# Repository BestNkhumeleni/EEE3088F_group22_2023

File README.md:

# EEE3088F_group22_2023
 With Best Nkhumeleni doing the STM32 intergration.
 Loic kibambo doing the power circutes.
 Maisha magavha doing the sensing

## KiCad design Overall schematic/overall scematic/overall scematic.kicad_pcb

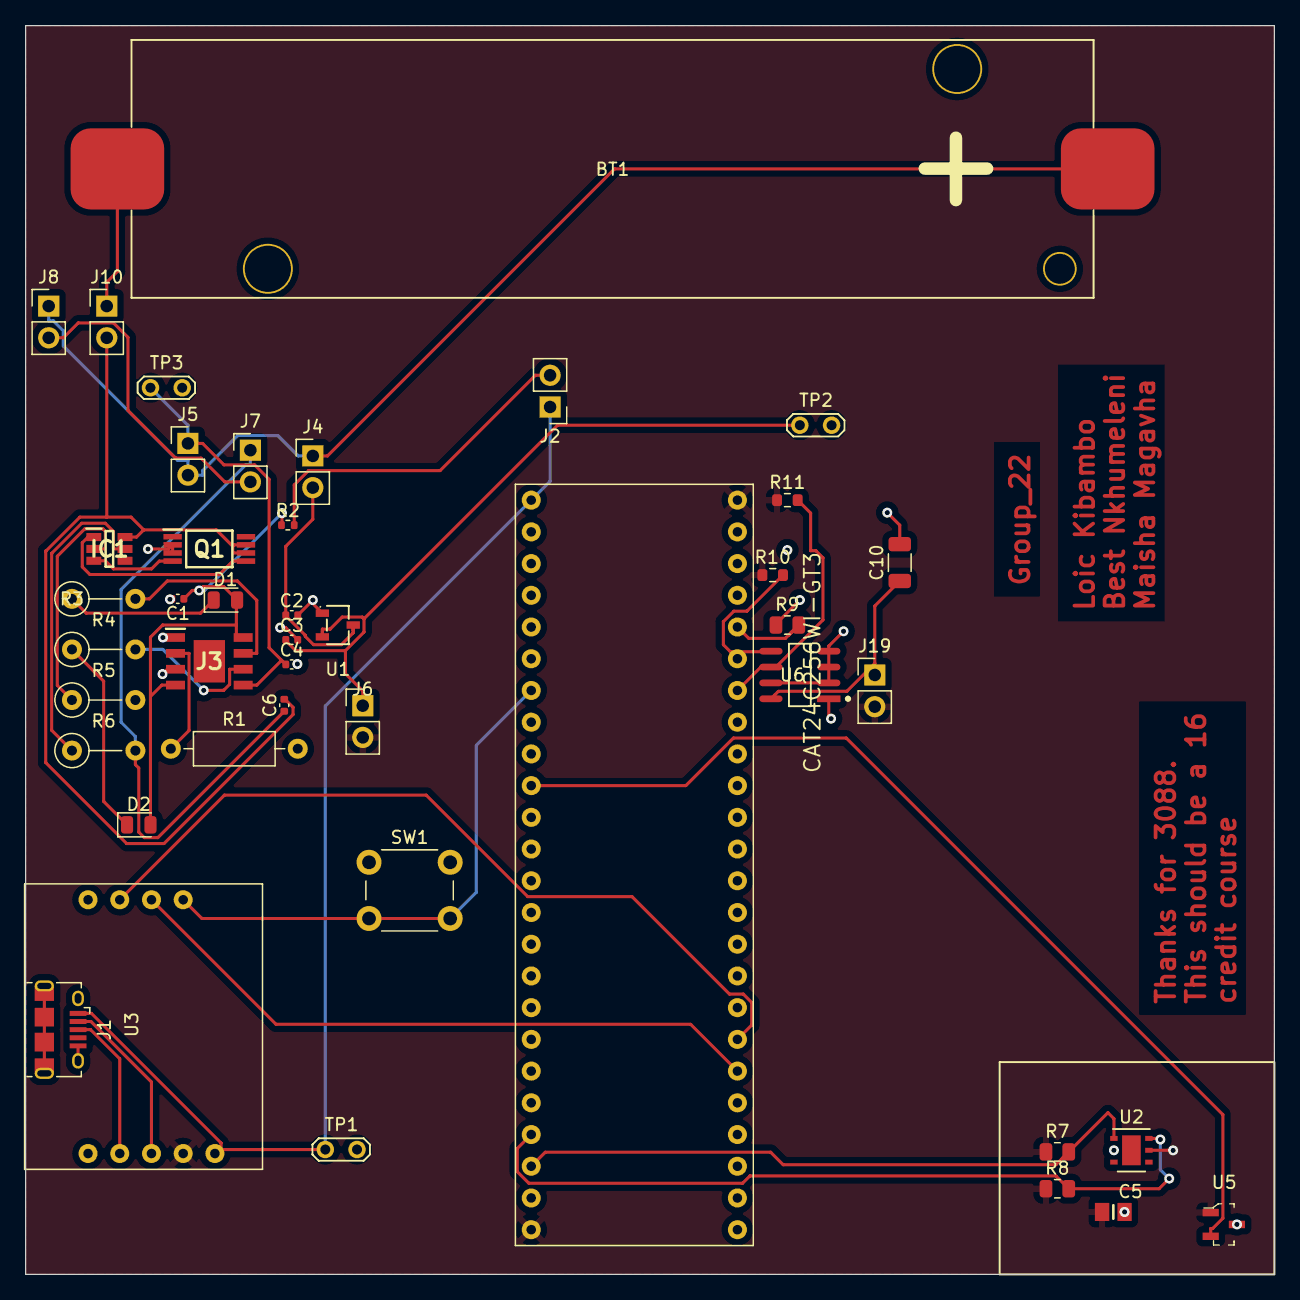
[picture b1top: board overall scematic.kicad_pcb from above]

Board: 2 copper layers, 100.0 x 100.0 mm, 43 parts (0 on the bottom side), 34 nets.

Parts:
BT1: Battery_Cell; 18650_Holder_SMD
C1, C4, C6: 10uf; C_0402_1005Metric
C2, C3: 1uf; C_0402_1005Metric
C5: CL21B104KCFNNNE; CAPC2012X140N
C10: 10nF; C_1206_3216Metric
D1: Green LED; D_0805_2012Metric
D2: Red LED; LED_0805_2012Metric
IC1: battery protection IC DW01A-G; DW01A
J1: USB_B_Micro; USB_Micro-B_Amphenol_10118194_Horizontal
J2, J4, J5, J6, J7, J8, J10: Conn_01x02_Pin; PinHeader_1x02_P2.54mm_Vertical
J3: Battery Charger IC TP4056; TP4056
J9: Conn_02x24_Counter_Clockwise; STM32F051C6T6
J19: C5116481; PinHeader_1x02_P2.54mm_Vertical
Q1: Dual Mosfet FS8205A; FB8205A
R1: 1.6k; R_Axial_DIN0207_L6.3mm_D2.5mm_P10.16mm_Horizontal
R2: 400m; R_0402_1005Metric
R3, R4, R5: 1k; R_Axial_DIN0207_L6.3mm_D2.5mm_P5.08mm_Vertical
R6: 100; R_Axial_DIN0207_L6.3mm_D2.5mm_P5.08mm_Vertical
R7, R8: 4.7k; R_0805_2012Metric
R9: 10k; R_0805_2012Metric
R10, R11: 1k; R_0603_1608Metric
SW1: SW_Push; SW_PUSH_6mm
TP1, TP2, TP3: TestPoint; TestPoint_2Pads_Pitch2.54mm_Drill0.8mm
U1: MCP1700T-3302E_TT; SOT-23-3_L2.9-W1.6-P1.90-LS2.8-BR
U2: HDC1080; Texas_PWSON-N6
U3: STLINK_UCT
U5: MCP9701AT-E_TT; SOT-23-3
U6: CAT24C256WI-GT3; ON_Semi-751BD-01-12_2008-O-0

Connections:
/Battery+: BT1.1 (+), J4.1, J5.2, J8.1
/Battery-: BT1.2 (-), J10.1
/Micro controller pin outs/BOOT: J9.44, R9.2
/Micro controller pin outs/NRST: J9.7, SW1.2, U3.6 (T_NRST)
/Micro controller pin outs/PA0: J9.10, U5.2 (VOUT)
/Micro controller pin outs/PA9: J9.30, U3.7 (T_SWCLK)
/Micro controller pin outs/PA10: J9.31, U3.8 (T_SWDIO)
/Micro controller pin outs/PB6: J9.42, R11.2, U6.6 (SCL)
/Micro controller pin outs/PB7: J9.43, R10.2, U6.5 (SDA)
/Power module/5V: J2.2, R2.2
/Power module/OC: IC1.3 (OC), Q1.4 (G1)
/Power module/OD: IC1.1 (OD), Q1.5 (G2)
/Power module/V_Battery: J7.2, J8.2
/Power module/Vcc_IC: C1.1, D1.2 (A), D2.2 (A), J3.4 (VCC4), J3.8 (CE), R2.1
/SCL: J9.21, R8.2, U2.6 (SCL)
/SDA: J9.22, R7.2, U2.1 (SDA)
/Supply_Voltage: C5.1, J6.2, J9.24, J9.48, J19.2, R7.1, R8.1, R10.1, R11.1, U2.5 (VCC), U3.2 (V_Target), U5.1 (VDD)
Data +: J1.3 (D+), U3.4 (USB_DP)
Data -: J1.2 (D-), U3.3 (USB_DM)
GND: C1.2, C2.2, C3.2, C4.2, C5.2, C10.2, J1.5 (GND), J1.6 (Shield), J3.1 (TEMP1), J3.3 (GND_3), J9.8, J9.23, J9.47, Q1.2 (S1_1), Q1.3 (S1_2), R1.2, R5.2, R9.1, SW1.1, U1.1 (GND), U2.2 (GND), U3.5 (GND), U5.3 (GND), U6.1 (A0), U6.2 (A1), U6.3 (A2), U6.4 (VSS), U6.7 (WP)
unnamed: D1.1 (K), R3.1
unnamed: D2.1 (K), R4.1
unnamed: IC1.2 (CS), R5.1
unnamed: C6.2, IC1.6 (GND), J10.2, Q1.6 (S2_1), Q1.7 (S2_2)
unnamed: IC1.5 (VCC), R6.1
unnamed: C4.1, J3.5 (BAT), J5.1, TP3.1
unnamed: J3.2 (PROG2), R1.1
unnamed: J3.7 (~CHRG), R3.2
unnamed: J3.6 (~STDBY), R4.2
unnamed: C2.1, J4.2, U1.3 (VIN)
unnamed: C3.1, J6.1, TP2.1, U1.2 (VOUT)
unnamed: C6.1, J7.1, R6.2
unnamed: C10.1, J19.1, U6.8 (VCC)
Vreg_Out: J1.1 (VBUS), J2.1, J9.1, TP1.1, U3.1 (5V_USB)

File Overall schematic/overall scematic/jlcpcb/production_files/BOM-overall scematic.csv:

Comment,Designator,Footprint,LCSC
4.7k,"R7,R8",R_0805_2012Metric,C101476
1uf,"C2,C3",C_0402_1005Metric,C14445
400m,R2,R_0402_1005Metric,C149632
MCP9701AT-E_TT,U5,SOT-23-3,C150830
10uf,"C1,C4,C6",C_0402_1005Metric,C15525
Dual Mosfet FS8205A,Q1,FB8205A,C16052
Battery Charger IC TP4056,J3,TP4056,C16581
10nF,C10,C_1206_3216Metric,C1846
SW_Push,SW1,SW_PUSH_6mm,C194405
1k,"R10,R11",R_0603_1608Metric,C21190
10k,R9,R_0805_2012Metric,C216802
CL21B104KCFNNNE,C5,CAPC2012X140N,C28233
Conn_01x02_Pin,"J10,J19,J2,J4,J5,J6,J7,J8",PinHeader_1x02_P2.54mm_Vertical,C3012204
 battery protection IC  DW01A-G,IC1,DW01A,C35306
MCP1700T-3302E_TT,U1,SOT-23-3_L2.9-W1.6-P1.90-LS2.8-BR,C39051
USB_B_Micro,J1,USB_Micro-B_Amphenol_10118194_Horizontal,C404969
CAT24C256WI-GT3,U6,ON_Semi-751BD-01-12_2008-O-0,C79987
HDC1080,U2,Texas_PWSON-N6,C82227
Red LED,D2,LED_0805_2012Metric,C84256

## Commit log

2023-02-25 Create stm32_code
2023-03-10 lets see
2023-03-10 sheets update
2023-03-12 updated interface
2023-03-12 updated proposal
2023-03-14 Add files via upload
    Updated BOM for Sensors
2023-03-14 updated BOM
2023-03-14 update kicad
2023-03-18 updated schematic
2023-03-19 Create Overall Schematic
2023-03-19 updated power sub
2023-03-19 fully annotated
2023-03-20 updated everything
2023-04-04 The final Gerber
2023-04-14 hail mary
2023-04-19 hello
2023-04-24 screen shots
2023-04-28 hail marry
2023-05-08 the j's
2023-05-13 let the code begin
2023-05-13 the code has begun
